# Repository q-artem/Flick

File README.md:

# Programmable-IR-keychain

Рендеры схем в папках плат

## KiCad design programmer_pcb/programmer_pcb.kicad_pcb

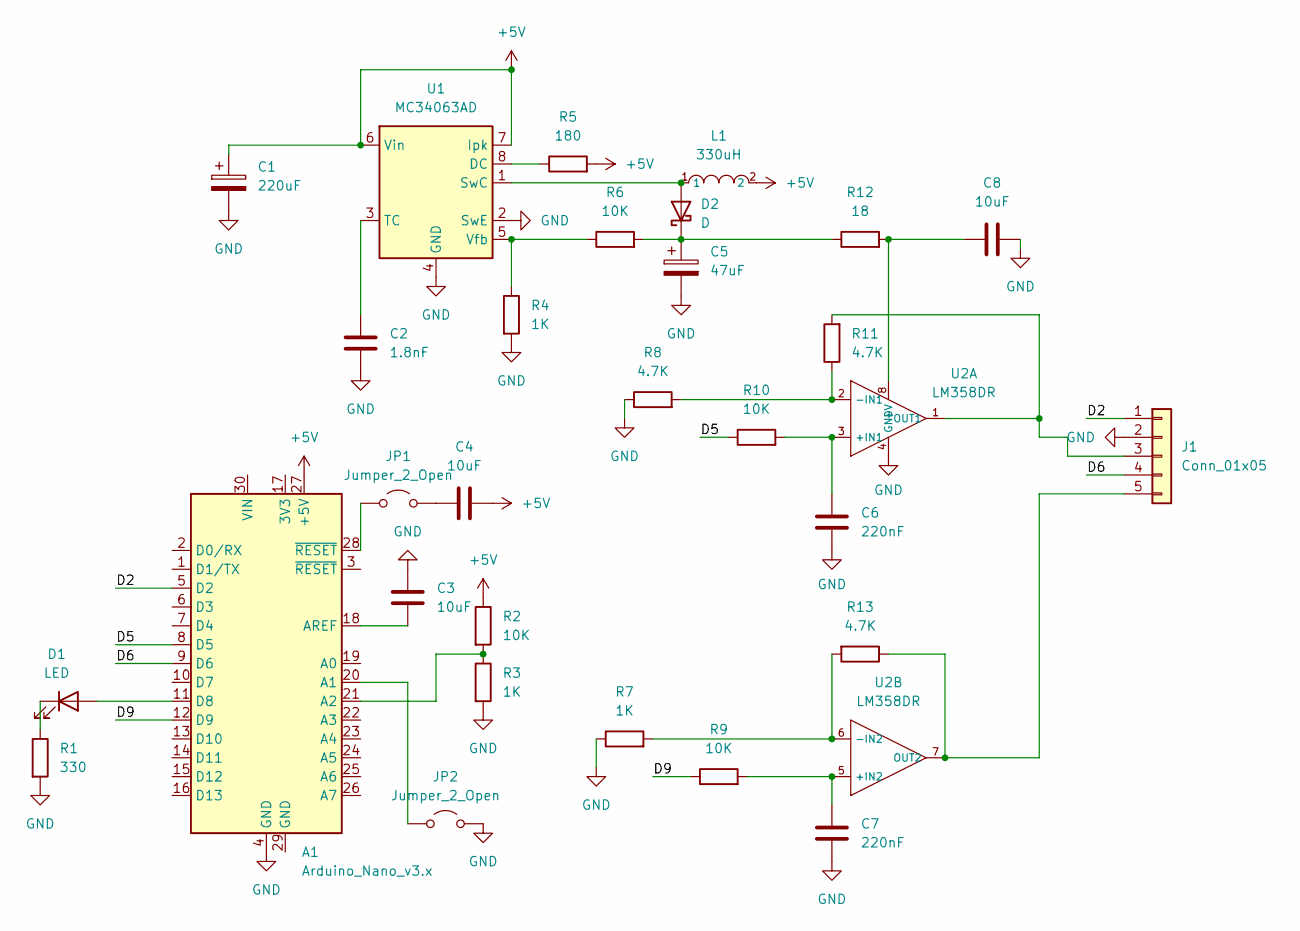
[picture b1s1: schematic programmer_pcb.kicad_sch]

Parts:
A1: Arduino_Nano_v3.x; Arduino_Nano
C1: 220uF; C_Elec_6.3x7.7
C2: 1.8nF; C_0805_2012Metric_Pad1.18x1.45mm_HandSolder
C3, C4, C8: 10uF; C_0805_2012Metric_Pad1.18x1.45mm_HandSolder
C5: 47uF; C_Elec_6.3x5.4
C6, C7: 220nF; C_0805_2012Metric_Pad1.18x1.45mm_HandSolder
D1: LED; LED_0805_2012Metric_Pad1.15x1.40mm_HandSolder
D2: D; D_SOD-123
J1: Conn_01x05; PinHeader_1x05_P2.54mm_Vertical
JP1, JP2: Jumper_2_Open; TestPoint_2Pads_Pitch2.54mm_Drill0.8mm
L1: 330uH; C1330209_IND-SMD_L7_8-W7_8_SDR0805; LCSC C1330209
R1: 330; R_0805_2012Metric_Pad1.20x1.40mm_HandSolder
R2, R6, R9, R10: 10K; R_0805_2012Metric_Pad1.20x1.40mm_HandSolder
R3, R4, R7: 1K; R_0805_2012Metric_Pad1.20x1.40mm_HandSolder
R5: 180; R_0805_2012Metric_Pad1.20x1.40mm_HandSolder
R8, R11, R13: 4.7K; R_0805_2012Metric_Pad1.20x1.40mm_HandSolder
R12: 18; R_0805_2012Metric_Pad1.20x1.40mm_HandSolder
U1: MC34063AD; SOIC-8_3.9x4.9mm_P1.27mm
U2: LM358DR; C5423_SOIC-8_L5_0-W4_0-P1_27-LS6_0-BL; LCSC C5423

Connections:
+5V: A1.27 (+5V), C1.1, C4.2, L1.2, R2.1, R5.2, U1.6 (Vin), U1.7 (Ipk)
/D2: A1.5 (D2), J1.1
/D5: A1.8 (D5), R10.1
/D6: A1.9 (D6), J1.4
/D9: A1.12 (D9), R9.1
GND: A1.4 (GND), C1.2, C2.2, C3.2, C5.2, C6.2, C7.2, C8.2, J1.2, JP2.2 (B), R1.2, R3.2, R4.2, R7.1, R8.1, U1.2 (SwE), U1.4 (GND), U2.4 (GND)
unnamed: A1.20 (A1), JP2.1 (A)
unnamed: A1.21 (A2), R2.2, R3.1
unnamed: A1.18 (AREF), C3.1
unnamed: A1.11 (D8), D1.2 (A)
unnamed: D1.1 (K), R1.1
unnamed: D2.2 (A), L1.1, U1.1 (SwC)
unnamed: C5.1, D2.1 (K), R6.2, R12.1
unnamed: J1.3, R11.2, U2.1 (OUT1)
unnamed: J1.5, R13.1, U2.7 (OUT2)
unnamed: A1.28 (~RESET), JP1.1 (A)
unnamed: C4.1, JP1.2 (B)
unnamed: R5.1, U1.8 (DC)
unnamed: C2.1, U1.3 (TC)
unnamed: R4.1, R6.1, U1.5 (Vfb)
unnamed: C6.1, R10.2, U2.3 (+IN1)
unnamed: C8.1, R12.2, U2.8 (+V)
unnamed: R8.2, R11.1, U2.2 (-IN1)
unnamed: C7.1, R9.2, U2.5 (+IN2)
unnamed: R7.2, R13.2, U2.6 (-IN2)

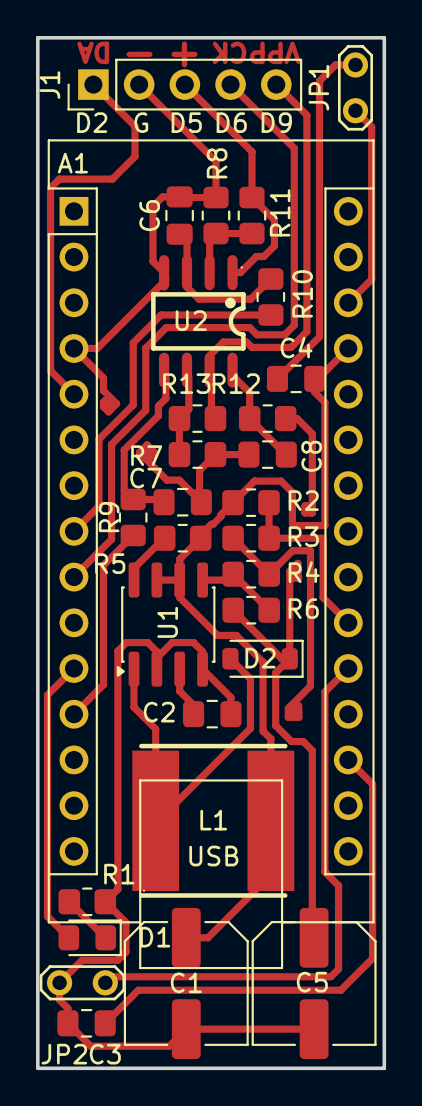
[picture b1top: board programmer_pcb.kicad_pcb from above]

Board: 2 copper layers, 19.2 x 57.2 mm, 30 parts (0 on the bottom side), 25 nets.

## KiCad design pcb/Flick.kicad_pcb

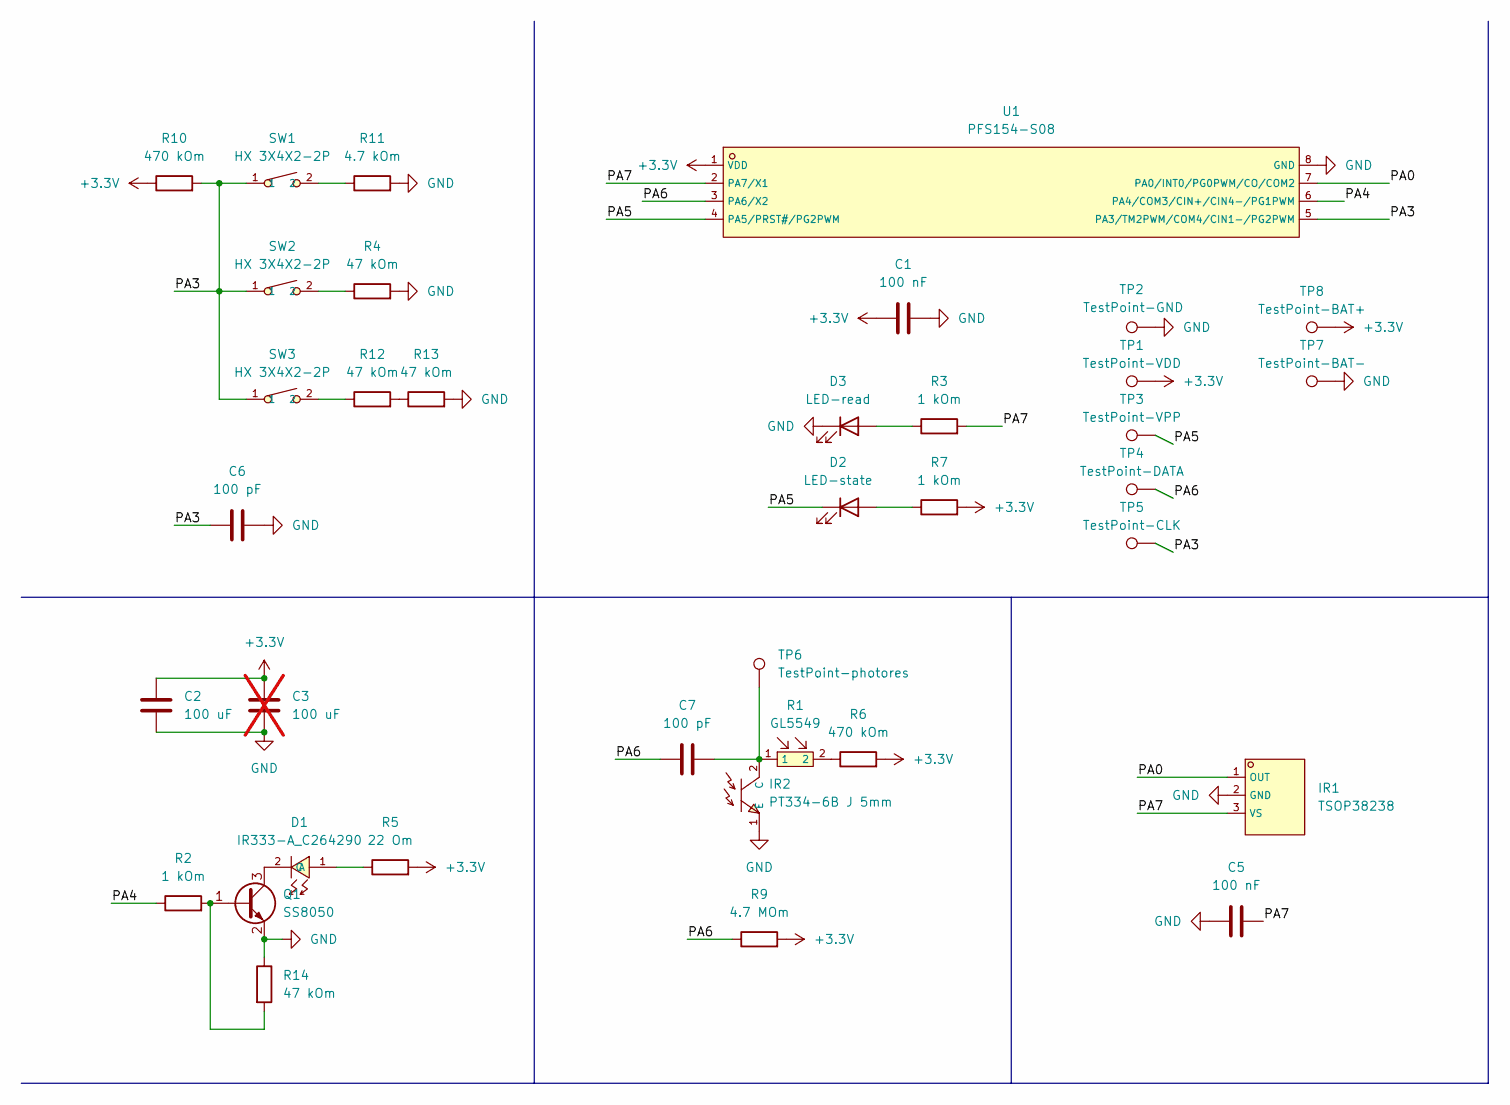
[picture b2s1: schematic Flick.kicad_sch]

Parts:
C1, C5: 100 nF; C_0603_1608Metric_Pad1.08x0.95mm_HandSolder
C2: 100 uF; C_1206_3216Metric_Pad1.33x1.80mm_HandSolder
C3: 100 uF; C_1206_3216Metric_Pad1.33x1.80mm_HandSolder; not fitted
C6, C7: 100 pF; C_0603_1608Metric_Pad1.08x0.95mm_HandSolder
D1: IR333-A_C264290; C264290_LED-TH_BD6_2-P2_54-FD; LCSC C264290
D2: LED-state; LED_0603_1608Metric_Pad1.05x0.95mm_HandSolder
D3: LED-read; LED_0603_1608Metric_Pad1.05x0.95mm_HandSolder
IR1: TSOP38238; C141632_SENSOR-TG_TSOP38236; LCSC C141632
IR2: PT334-6B J 5mm; C60395_OPTO-TH_BD5_9-P2_54-L; LCSC C60395
Q1: SS8050; SOT-23
R1: GL5549; C125631_RES-TH_L5_1-W4_3-P3_40-D0_5; LCSC C125631
R2, R3, R7: 1 kOm; R_0603_1608Metric_Pad0.98x0.95mm_HandSolder
R4, R12, R13, R14: 47 kOm; R_0603_1608Metric_Pad0.98x0.95mm_HandSolder
R5: 22 Om; R_0603_1608Metric_Pad0.98x0.95mm_HandSolder
R6, R10: 470 kOm; R_0603_1608Metric_Pad0.98x0.95mm_HandSolder
R9: 4.7 MOm; R_0603_1608Metric_Pad0.98x0.95mm_HandSolder
R11: 4.7 kOm; R_0603_1608Metric_Pad0.98x0.95mm_HandSolder
SW1, SW2, SW3: HX 3X4X2-2P; C49234124_KEY-SMD_L4_0-W3_0-LS4_9-1; LCSC C49234124
TP1: TestPoint-VDD; TestPoint_Pad_D1.5mm
TP2: TestPoint-GND; TestPoint_Pad_D1.5mm
TP3: TestPoint-VPP; TestPoint_Pad_D1.5mm
TP4: TestPoint-DATA; TestPoint_Pad_D1.5mm
TP5: TestPoint-CLK; TestPoint_Pad_D1.5mm
TP6: TestPoint-photores; TestPoint_Pad_D1.5mm
TP7: TestPoint-BAT-; TestPoint_Keystone_5015_Micro_Mini
TP8: TestPoint-BAT+; TestPoint_Keystone_5015_Micro_Mini
U1: PFS154-S08; C317611_SOP-8_L4_9-W3_9-P1_27-LS6_0-BL; LCSC C317611

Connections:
+3.3V: C1.1, C2.1, C3.1, R5.2, R6.2, R7.2, R9.2, R10.1, TP1.1 (1_1), TP8.1 (1_1), U1.1 (VDD)
/PA0: IR1.1 (OUT), U1.7 (PA0/INT0/PG0PWM/CO/COM2)
/PA3: C6.1, R10.2, SW1.1, SW2.1, SW3.1, TP5.1 (1_1), U1.5 (PA3/TM2PWM/COM4/CIN1-/PG2PWM)
/PA4: R2.1, U1.6 (PA4/COM3/CIN+/CIN4-/PG1PWM)
/PA5: D2.1 (K), TP3.1 (1_1), U1.4 (PA5/PRST#/PG2PWM)
/PA6: C7.1, R9.1, TP4.1 (1_1), U1.3 (PA6/X2)
/PA7: C5.2, IR1.3 (VS), R3.2, U1.2 (PA7/X1)
GND: C1.2, C2.2, C3.2, C5.1, C6.2, D3.1 (K), IR1.2 (GND), IR2.1 (E), Q1.2 (E), R4.2, R11.2, R13.2, R14.1, TP2.1 (1_1), TP7.1 (1_1), U1.8 (GND)
unnamed: D1.1 (A), R5.1
unnamed: D1.2 (C), Q1.3 (C)
unnamed: D2.2 (A), R7.1
unnamed: D3.2 (A), R3.1
unnamed: C7.2, IR2.2 (C), R1.1, TP6.1 (1_1)
unnamed: Q1.1 (B), R2.2, R14.2
unnamed: R1.2, R6.1
unnamed: R4.1, SW2.2
unnamed: R11.1, SW1.2
unnamed: R12.1, SW3.2
unnamed: R12.2, R13.1

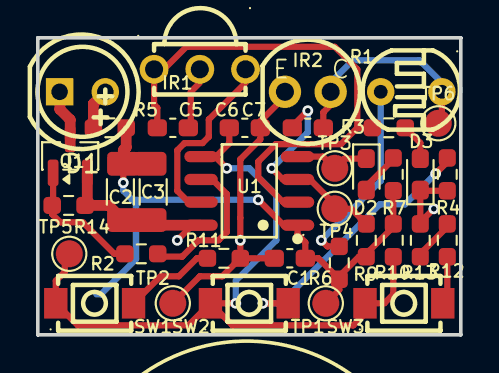
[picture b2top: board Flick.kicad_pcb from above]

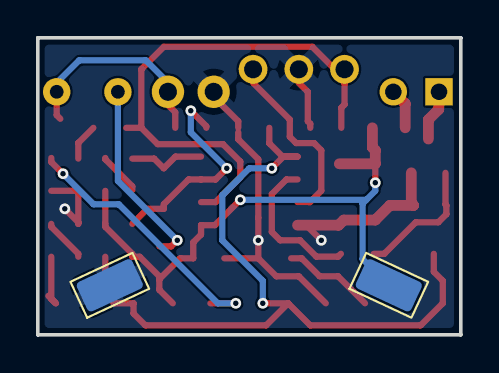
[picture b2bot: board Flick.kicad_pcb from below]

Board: 2 copper layers, 23.5 x 16.5 mm, 37 parts (2 on the bottom side), 19 nets.
